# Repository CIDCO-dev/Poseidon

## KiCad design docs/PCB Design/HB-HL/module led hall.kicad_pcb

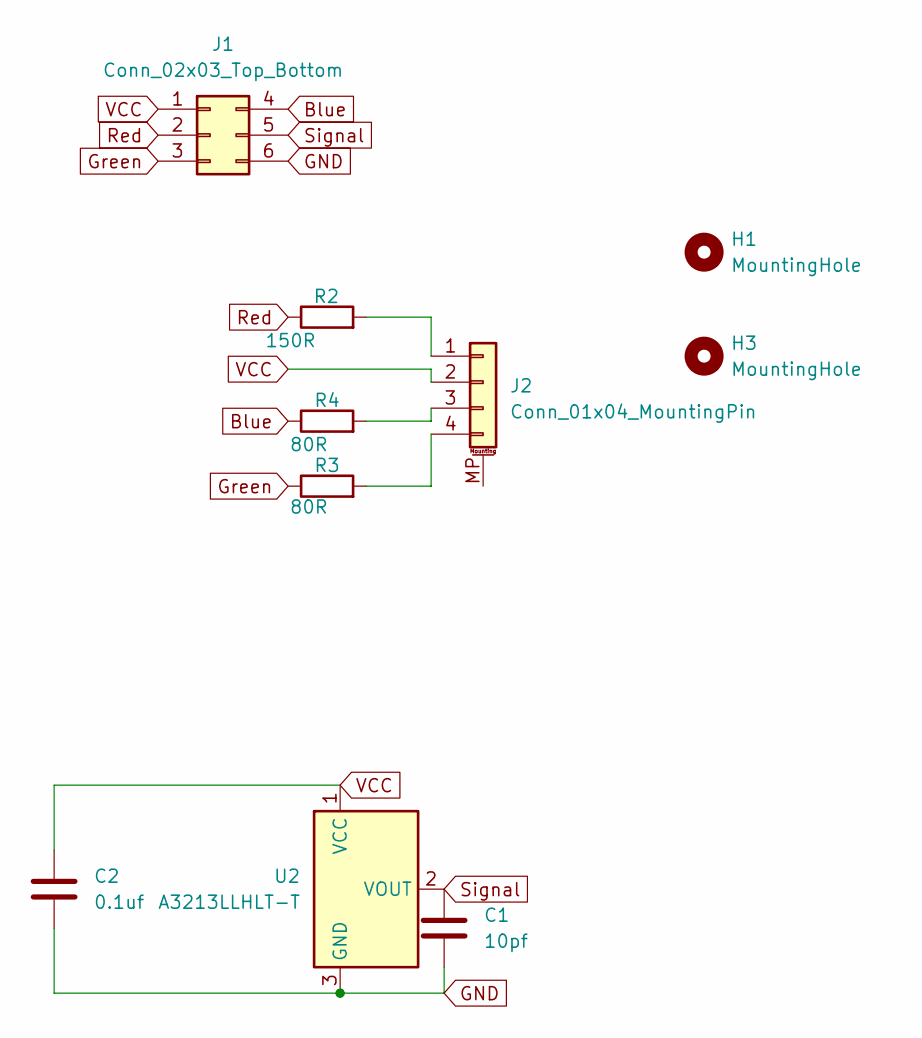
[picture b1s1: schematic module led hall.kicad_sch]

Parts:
C1: 10pf; C_1206_3216Metric
C2: 0.1uf; C_1206_3216Metric
H1, H3: MountingHole; MountingHole_4.3mm_M4
J1: Conn_02x03_Top_Bottom; IDC-Header_2x03_P2.54mm_Vertical
J2: Conn_01x04_MountingPin; TE_84952-4_1x04-1MP_P1.0mm_Horizontal
R2: 150R; R_1206_3216Metric
R3, R4: 80R; R_1206_3216Metric
U2: A3213LLHLT-T; SOT-23W

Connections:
Blue: J1.4, R4.1
GND: C1.2, C2.2, J1.6, U2.3 (GND)
Green: J1.3, R3.1
unnamed: J2.1, R2.2
unnamed: J2.3, R4.2
unnamed: J2.4, R3.2
Red: J1.2, R2.1
Signal: C1.1, J1.5, U2.2 (VOUT)
VCC: C2.1, J1.1, J2.2, U2.1 (VCC)

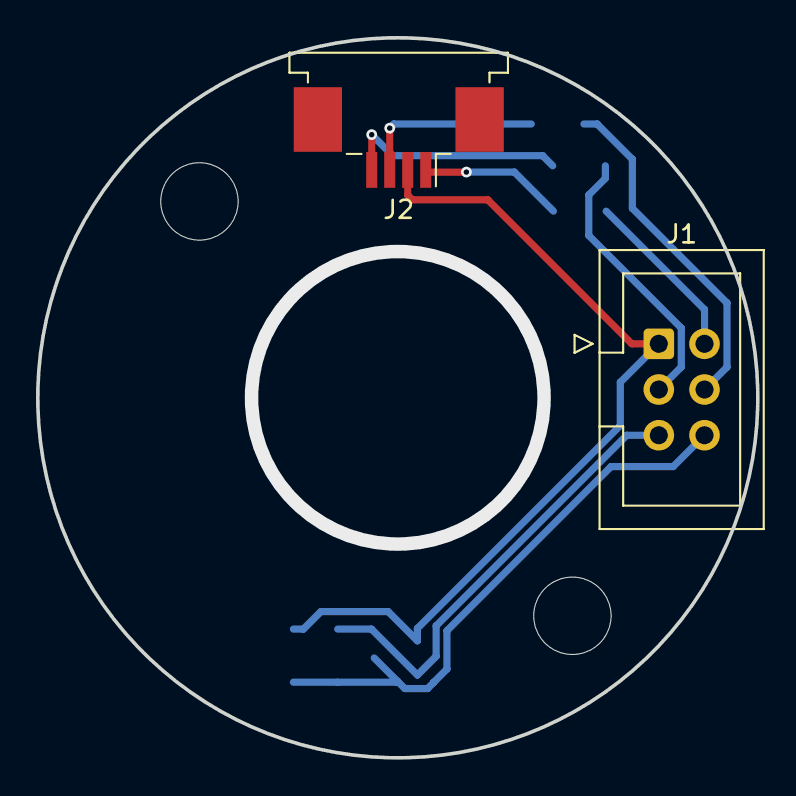
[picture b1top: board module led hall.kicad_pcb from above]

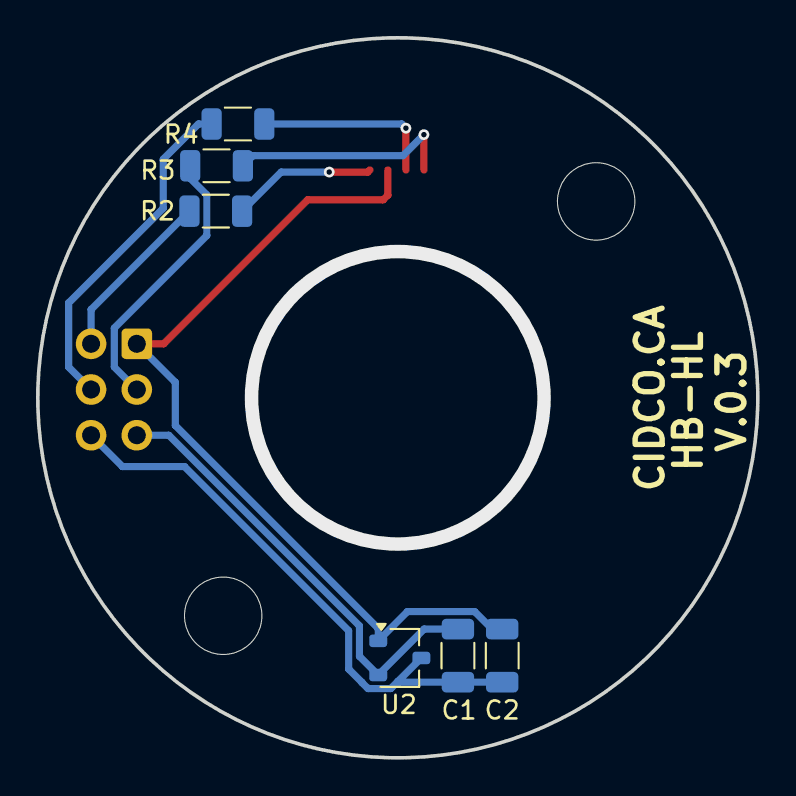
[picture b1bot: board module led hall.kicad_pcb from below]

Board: 2 copper layers, 40.0 x 40.0 mm, 10 parts (6 on the bottom side), 9 nets.

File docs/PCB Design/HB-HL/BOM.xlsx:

Comment | Designator | Footprint | JLCPCB Part #（optional）
Conn_01x04_MountingPin | J2 | TE_84952-4_1x04-1MP_P1.0mm_Horizontal | C262731
80R | R3,R4 | R_1206_3216Metric | C270896
10pf | C1 | C_1206_3216Metric | C377016
150R | R2 | R_1206_3216Metric | C2907432
A3213LLHLT-T | U2 | SOT-23W | C75884
0.1uf | C2 | C_1206_3216Metric | C841554

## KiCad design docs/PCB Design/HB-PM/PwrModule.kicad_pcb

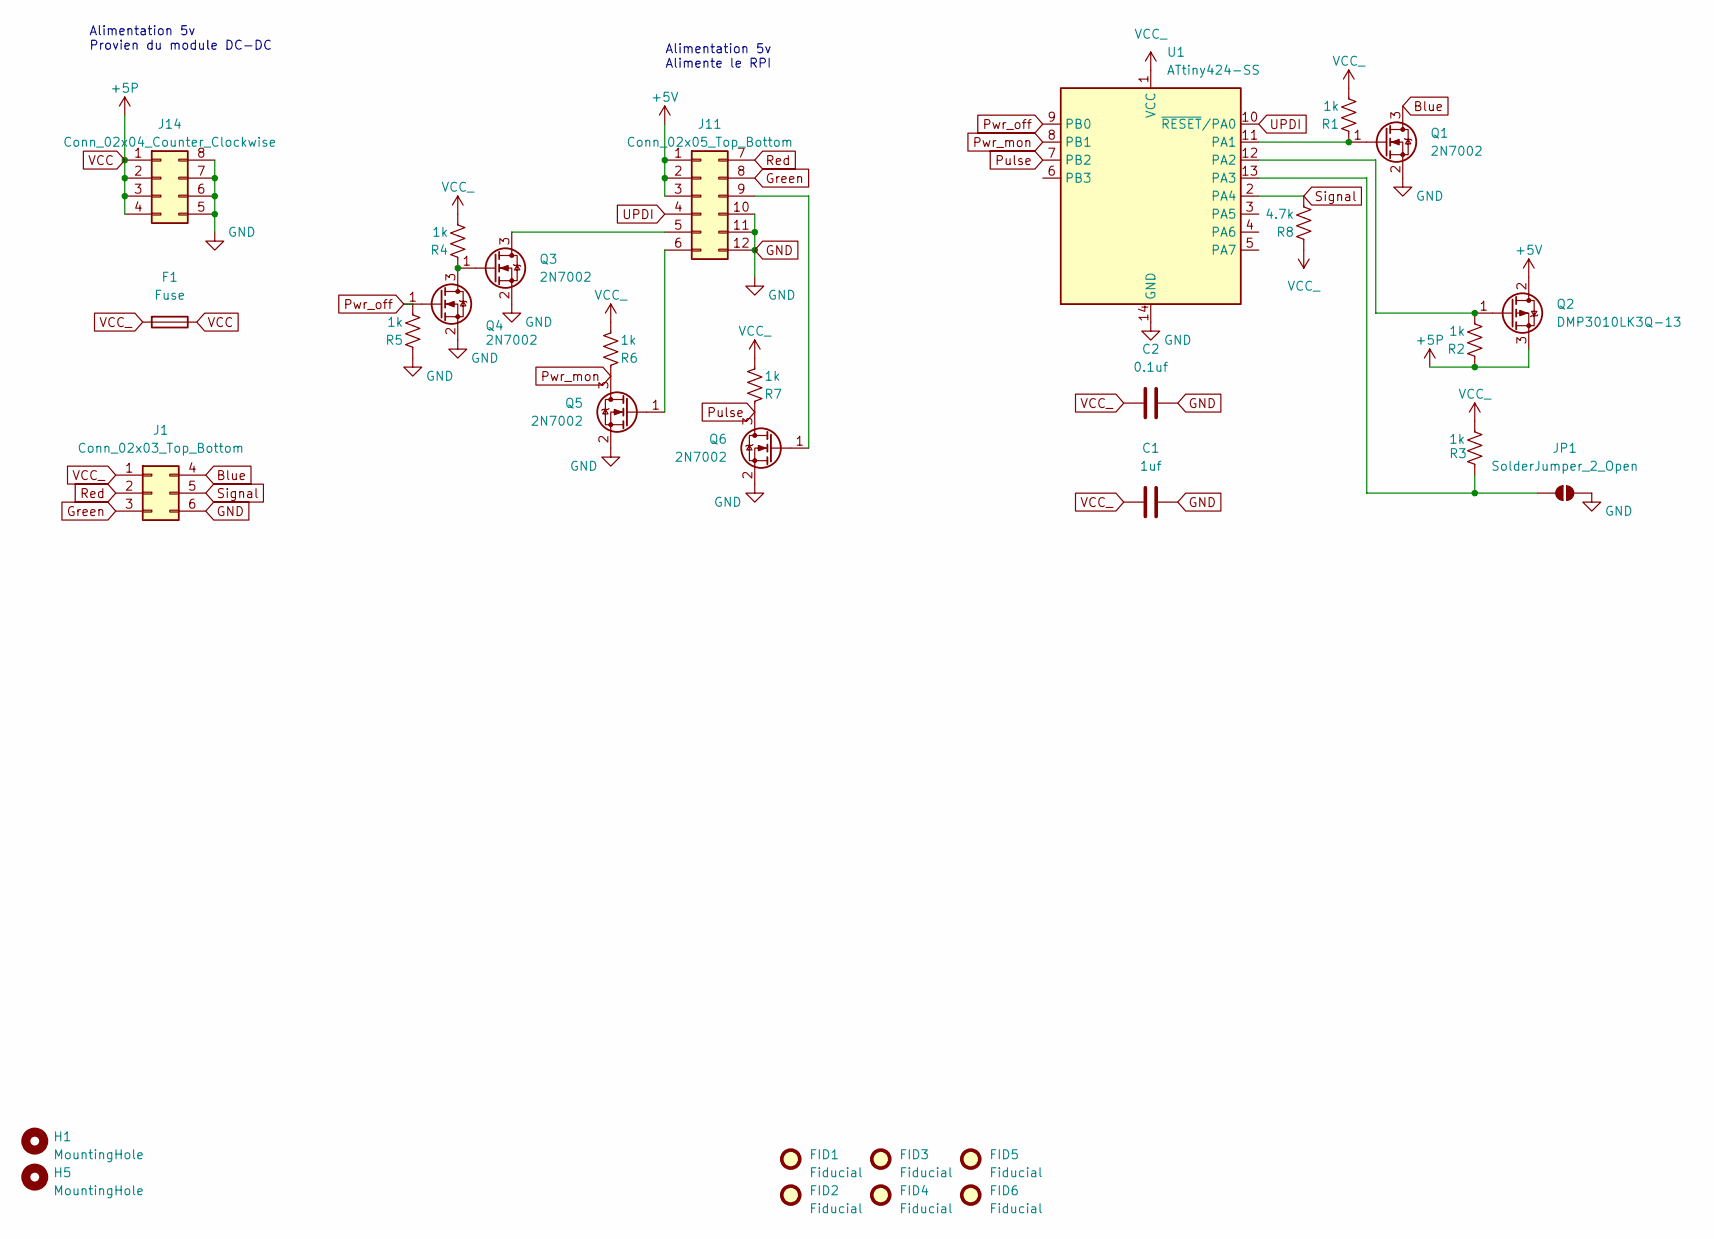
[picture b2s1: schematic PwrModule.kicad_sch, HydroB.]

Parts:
C1: 1uf; C_1206_3216Metric
C2: 0.1uf; C_1206_3216Metric
F1: Fuse; Fuse_1206_3216Metric
FID1, FID2, FID3, FID4, FID5, FID6: Fiducial; Fiducial_0.75mm_Mask2.25mm
H1, H5: MountingHole; MountingHole_2.7mm_M2.5_ISO7380_Pad
J1: Conn_02x03_Top_Bottom; IDC-Header_2x03_P2.54mm_Vertical
J11: Conn_02x05_Top_Bottom; PinHeader_2x06_P2.54mm_Vertical
J14: Conn_02x04_Counter_Clockwise; PinHeader_2x04_P2.54mm_Vertical
JP1: SolderJumper_2_Open; SolderJumper-2_P1.3mm_Open_TrianglePad1.0x1.5mm
Q1, Q3, Q4, Q5, Q6: 2N7002; SOT-23
Q2: DMP3010LK3Q-13; TO-252-2
R1, R2, R3, R4, R5, R6, R7: 1k; R_1206_3216Metric
R8: 4.7k; R_1206_3216Metric
U1: ATtiny424-SS; SOIC-14_3.9x8.7mm_P1.27mm

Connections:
+5V: J11.1, J11.2, J11.3, Q2.2 (D)
Blue: J1.4, Q1.3 (D)
GND: C1.1, C2.1, J1.6, J11.10, J11.11, J11.12, J14.5, J14.6, J14.7, J14.8, JP1.2 (B), Q1.2 (S), Q3.2 (S), Q4.2 (S), Q5.2 (S), Q6.2 (S), R5.1, U1.14 (GND)
Green: J1.3, J11.8
unnamed: J11.5, Q3.3 (D)
unnamed: J11.6, Q5.1 (G)
unnamed: J11.9, Q6.1 (G)
unnamed: JP1.1 (A), R3.1, U1.13 (PA3)
unnamed: Q1.1 (G), R1.1, U1.11 (PA1)
unnamed: Q2.1 (G), R2.2, U1.12 (PA2)
unnamed: Q3.1 (G), Q4.3 (D), R4.1
Pulse: Q6.3 (D), R7.1, U1.7 (PB2)
Pwr_mon: Q5.3 (D), R6.1, U1.8 (PB1)
Pwr_off: Q4.1 (G), R5.2, U1.9 (PB0)
Red: J1.2, J11.7
Signal: J1.5, R8.2, U1.2 (PA4)
UPDI: J11.4, U1.10 (~RESET/PA0)
VCC: F1.1, J14.1, J14.2, J14.3, J14.4, Q2.3 (S), R2.1
VCC_: C1.2, C2.2, F1.2, J1.1, R1.2, R3.2, R4.2, R6.2, R7.2, R8.1, U1.1 (VCC)

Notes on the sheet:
Alimentation 5v Alimente le RPI
Alimentation 5v Provien du module DC-DC

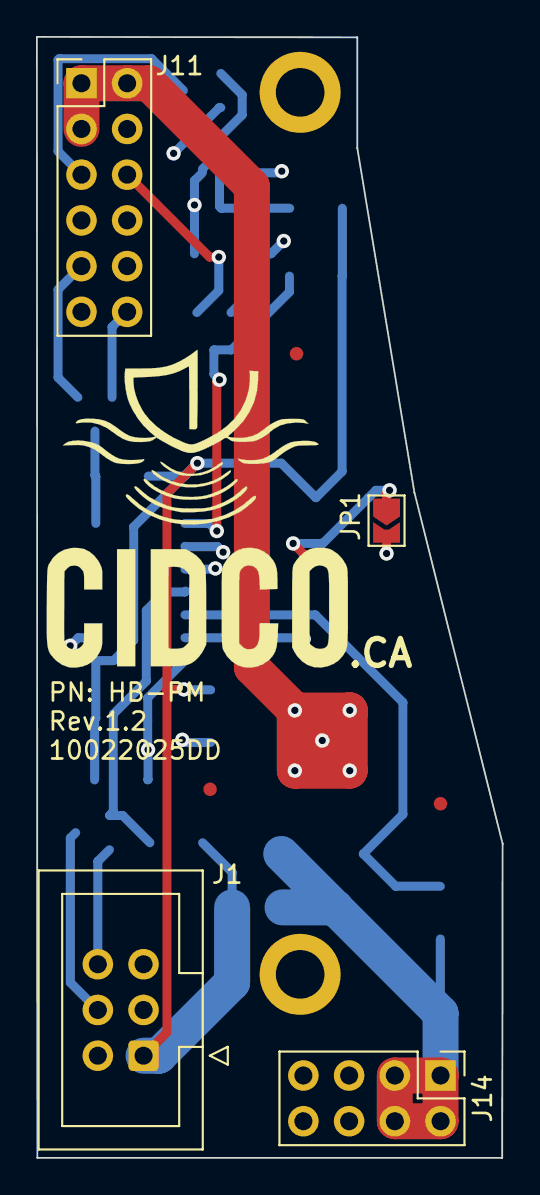
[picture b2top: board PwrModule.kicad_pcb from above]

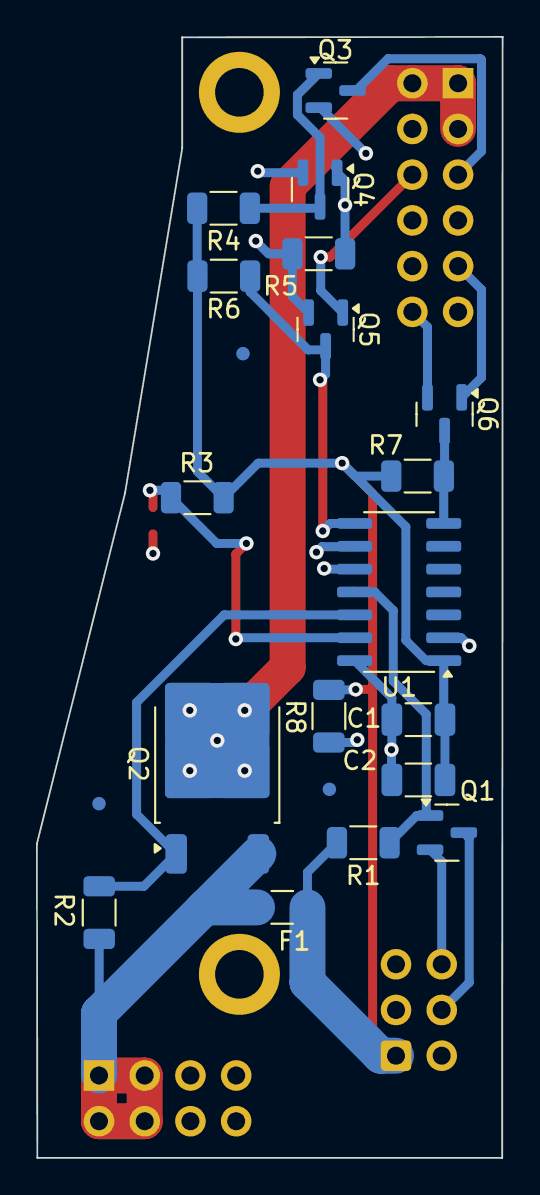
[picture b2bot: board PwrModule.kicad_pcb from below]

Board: 4 copper layers, 25.9 x 62.3 mm, 31 parts (21 on the bottom side), 19 nets.

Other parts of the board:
logo1: LOGO; logo cidco

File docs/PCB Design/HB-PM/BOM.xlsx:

Comment | Designator | Footprint | JLCPCB Part #（optional）
1uf | C1 | C_1206_3216Metric | C377070
1k | R2,R5,R3,R7,R1,R6,R4 | R_1206_3216Metric | C2889701
Fuse | F1 | Fuse_1206_3216Metric | C182308
DMP3010LK3Q-13 | Q2 | TO-252-2 | C461089
2N7002 | Q1,Q6,Q4,Q3,Q5 | SOT-23 | C22446827
0.1uf | C2 | C_1206_3216Metric | C841554
4.7k | R8 | R_1206_3216Metric | C2907499
ATtiny424-SS | U1 | SOIC-14_3.9x8.7mm_P1.27mm | C3234243

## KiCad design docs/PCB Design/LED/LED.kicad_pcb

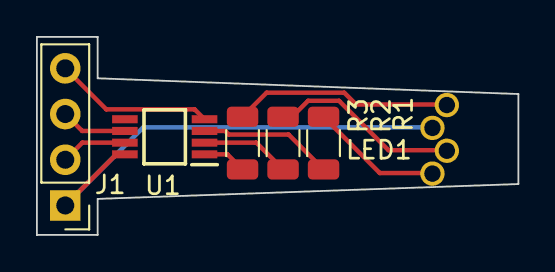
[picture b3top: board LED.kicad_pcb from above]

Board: 2 copper layers, 26.7 x 11.0 mm, 6 parts (0 on the bottom side), 10 nets.

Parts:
J1: Conn_01x04; PinHeader_1x04_P2.54mm_Vertical
LED1: HV-5RGB60; HV5RGB25
R1, R2, R3: R_US; R_1206_3216Metric
U1: PCA9533DP_02,118; SOP65P490X110-8N

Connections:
GND: J1.4, U1.4 (VSS)
unnamed: J1.1, LED1.3 (COMMON_CATHODE), U1.8 (VDD)
unnamed: J1.2, U1.7 (SDA)
unnamed: J1.3, U1.6 (SCL)
unnamed: LED1.1 (ANODE_BLUE), R1.1
unnamed: LED1.4 (ANODE_GREEN), R3.1
unnamed: LED1.2 (ANODE_RED), R2.1
unnamed: R3.2, U1.1 (LED0)
unnamed: R2.2, U1.2 (LED1)
unnamed: R1.2, U1.3 (LED2)

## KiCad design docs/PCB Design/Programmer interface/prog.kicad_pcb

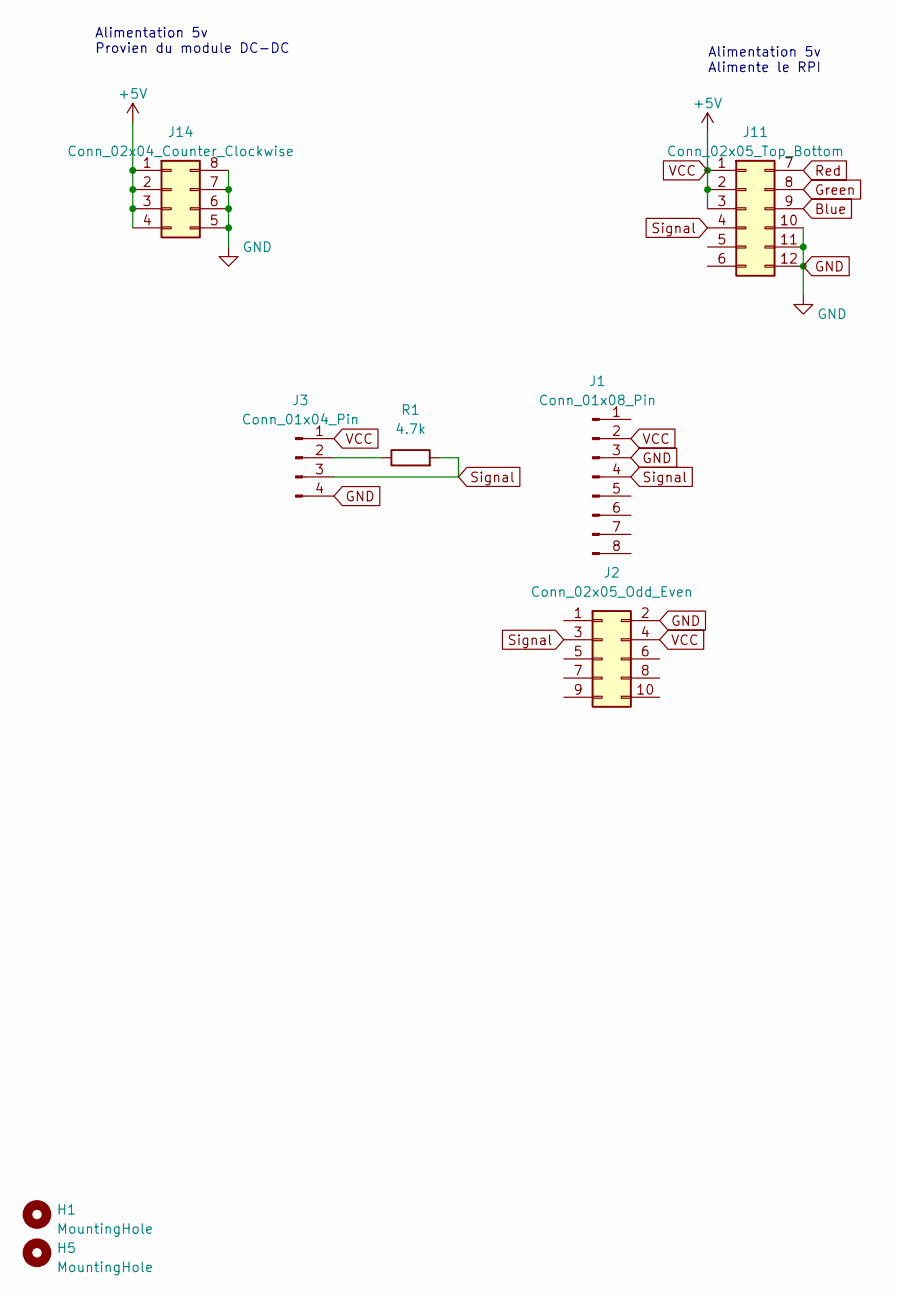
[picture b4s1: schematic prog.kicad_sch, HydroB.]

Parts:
H1, H5: MountingHole; MountingHole_2.7mm_M2.5_ISO7380_Pad
J1: Conn_01x08_Pin; PinHeader_1x08_P2.54mm_Horizontal
J2: Conn_02x05_Odd_Even; IDC-Header_2x05_P2.54mm_Vertical
J3: Conn_01x04_Pin; PinHeader_1x04_P2.54mm_Horizontal
J11: Conn_02x05_Top_Bottom; PinHeader_2x06_P2.54mm_Vertical
J14: Conn_02x04_Counter_Clockwise; PinHeader_2x04_P2.54mm_Vertical
R1: 4.7k; R_1206_3216Metric_Pad1.30x1.75mm_HandSolder

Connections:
Blue: J11.9
GND: J1.3, J2.2, J3.4, J11.10, J11.11, J11.12, J14.5, J14.6, J14.7, J14.8
Green: J11.8
unnamed: J3.2, R1.1
Red: J11.7
Signal: J1.4, J2.3, J3.3, J11.4, R1.2
VCC: J1.2, J2.4, J3.1, J11.1, J11.2, J11.3, J14.1, J14.2, J14.3, J14.4

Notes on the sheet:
Alimentation 5v Alimente le RPI
Alimentation 5v Provien du module DC-DC

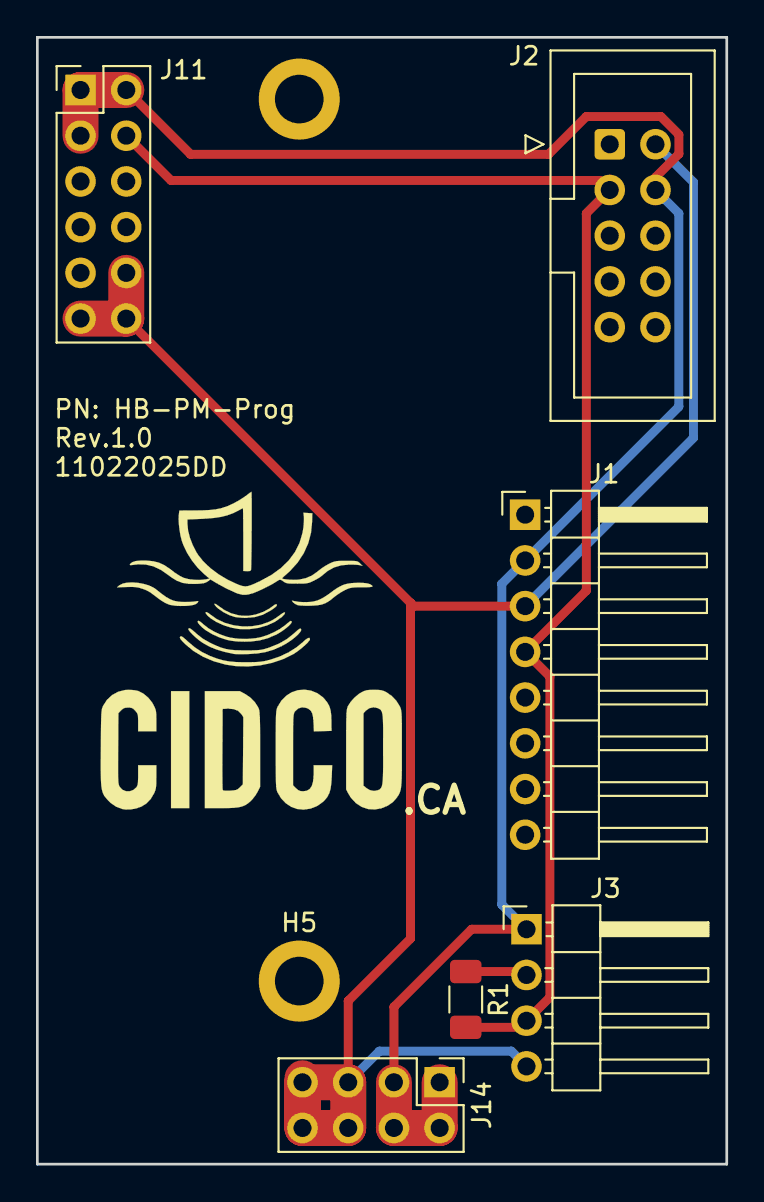
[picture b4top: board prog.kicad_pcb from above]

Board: 2 copper layers, 38.3 x 62.6 mm, 9 parts (0 on the bottom side), 4 nets.

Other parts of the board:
logo1: LOGO; logo cidco

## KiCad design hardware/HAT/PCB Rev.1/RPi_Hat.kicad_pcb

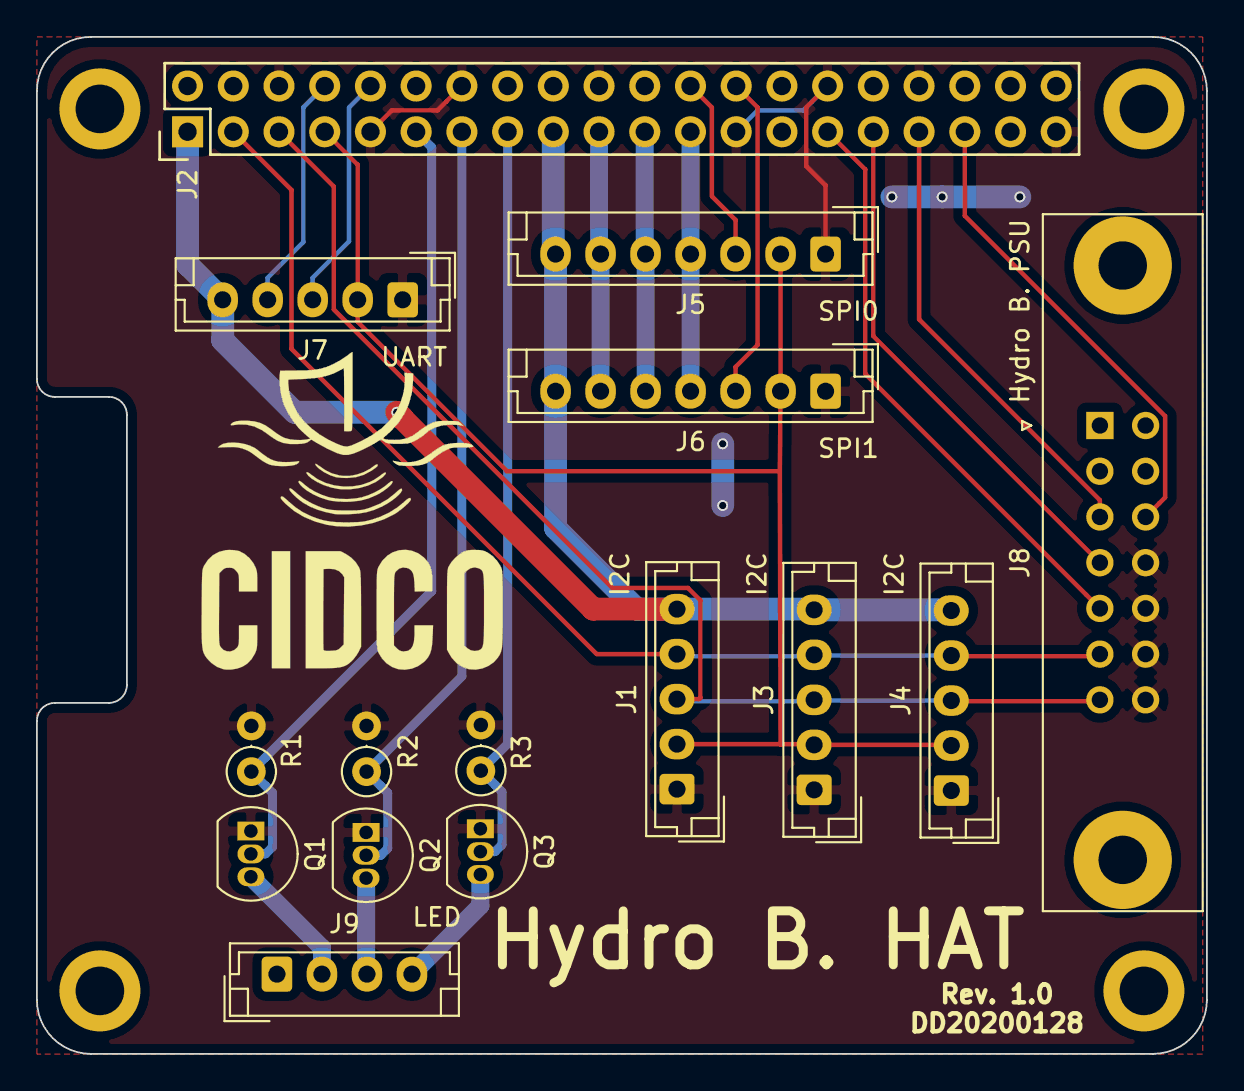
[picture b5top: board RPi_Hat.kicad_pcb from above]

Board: 2 copper layers, 65.0 x 56.5 mm, 15 parts (0 on the bottom side), 23 nets.

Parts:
J1, J3, J4, J7: Conn_01x05; JST_EH_B5B-EH-A_1x05_P2.50mm_Vertical
J2: RPi_GPIO; Pin_Header_Straight_2x20
J5, J6: Conn_01x07; JST_EH_B7B-EH-A_1x07_P2.50mm_Vertical
J8: Conn_02x07_Odd_Even; IDC-Header_2x07_P2.54mm_Vertical_Lock
J9: Conn_01x04; JST_EH_B4B-EH-A_1x04_P2.50mm_Vertical
Q1, Q2, Q3: 2N7000; TO-92_Inline
R1, R2, R3: 1k; R_Axial_DIN0207_L6.3mm_D2.5mm_P2.54mm_Vertical

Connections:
3.3V: J1.5, J2.1, J2.17, J3.5, J4.5, J5.7, J6.7, J7.5
5V: J2.2, J2.4, J8.1, J8.2, J8.3, J8.4, J9.1
12V_ON: J2.35, J8.6
24V_ON: J2.33, J8.5
C0: J2.24, J5.3
C1: J2.26, J6.3
GND: J1.1, J2.6, J2.9, J2.14, J2.20, J2.25, J2.30, J2.34, J2.39, J3.1, J4.1, J5.1, J6.1, J7.1, J8.8, J8.10, J8.12, J8.14, Q1.1, Q2.1, Q3.1, R1.2, R2.2, R3.2
LEDB: J2.15, Q3.2, R3.1
LEDG: J2.13, Q2.2, R2.1
LEDR: J2.11, Q1.2, R1.1
MISO: J2.21, J5.5, J6.5
MOSI: J2.19, J5.6, J6.6
unnamed: J9.2, Q1.3
unnamed: J9.3, Q2.3
unnamed: J9.4, Q3.3
PPS: J1.2, J2.7, J3.2, J4.2, J5.2, J6.2, J7.2
RPI_PWR_OK: J2.31, J8.7
RPI_SHDWN: J2.29, J8.9
RX: J2.10, J7.3
SCL: J1.3, J2.5, J3.3, J4.3, J8.13
SCLK: J2.23, J5.4, J6.4
SDA: J1.4, J2.3, J3.4, J4.4, J8.11
TX: J2.8, J7.4

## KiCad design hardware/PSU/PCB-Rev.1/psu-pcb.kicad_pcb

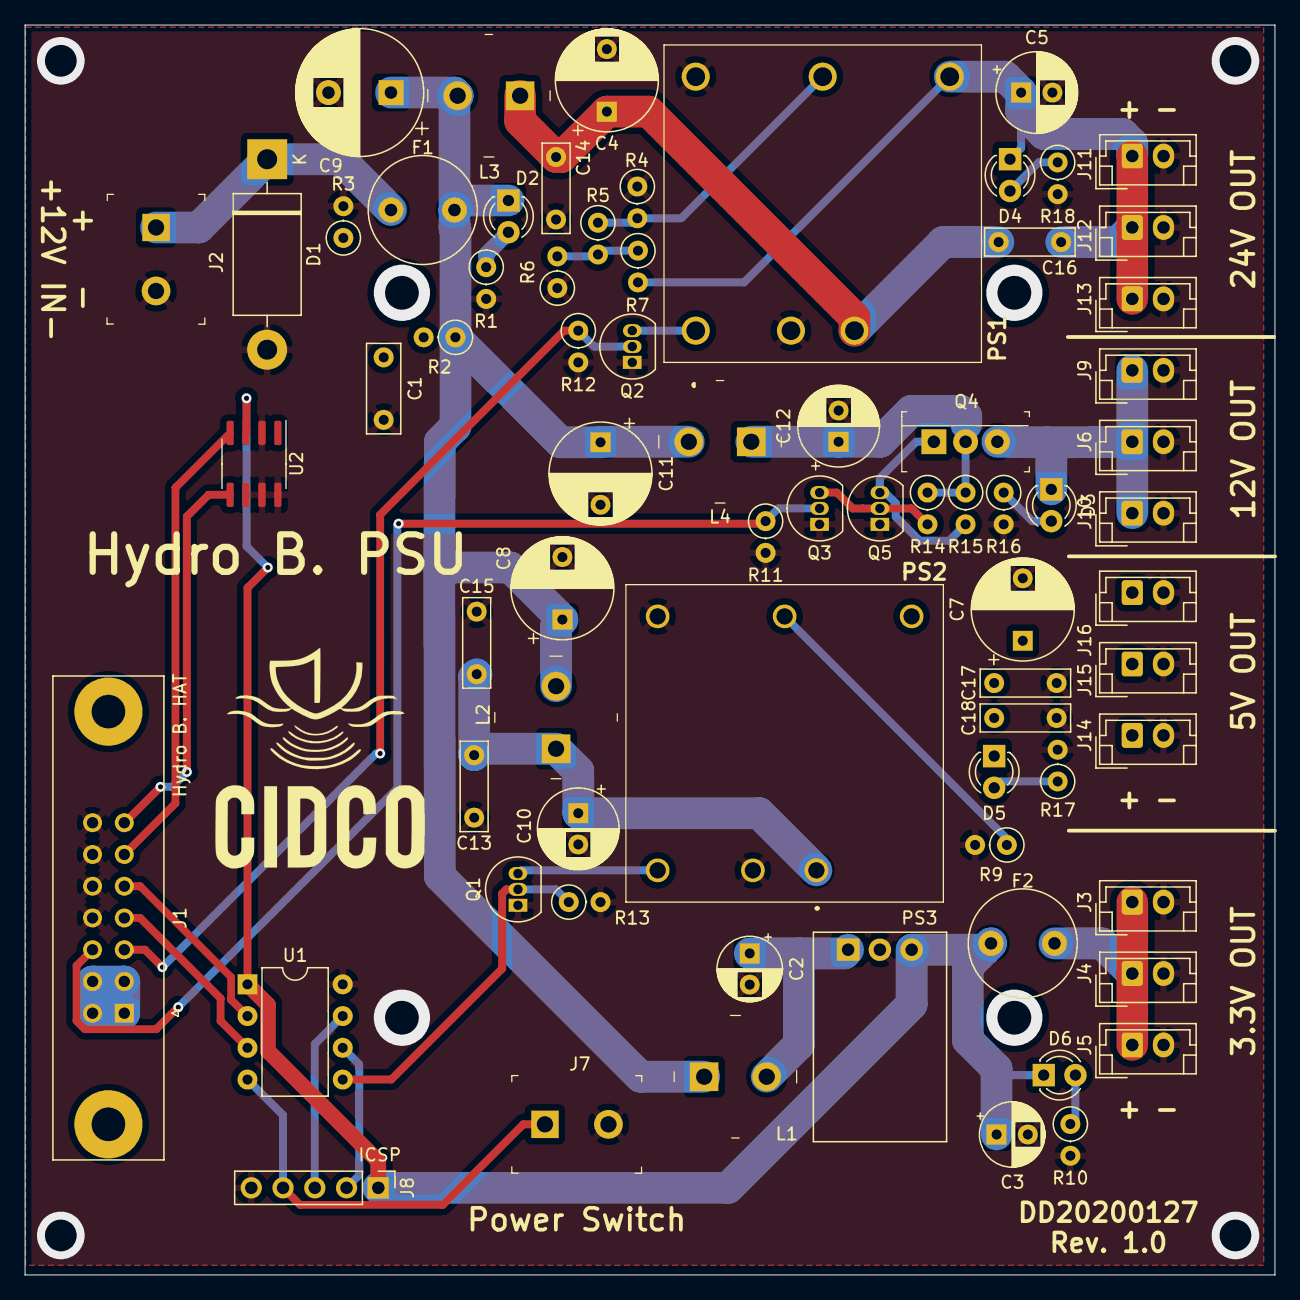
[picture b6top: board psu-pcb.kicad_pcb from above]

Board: 2 copper layers, 100.0 x 100.0 mm, 72 parts (0 on the bottom side), 34 nets.

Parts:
C1: 0.1u; C_Rect_L7.0mm_W2.5mm_P5.00mm
C2: 10u 35v; CP_Radial_D5.0mm_P2.50mm
C3: 10u 10v; CP_Radial_D5.0mm_P2.50mm
C4, C11: 100UF 50V; CP_Radial_D8.0mm_P5.00mm
C5, C12: 47UF 50V; CP_Radial_D6.3mm_P2.50mm
C7: 330uf 16v; CP_Radial_D8.0mm_P5.00mm
C8: 100UF 35V; CP_Radial_D8.0mm_P5.00mm
C9: 330UF 50V; CP_Radial_D10.0mm_P5.00mm
C10: 47UF 35V; CP_Radial_D6.3mm_P2.50mm
C13, C17: 10UF; C_Rect_L7.0mm_W2.0mm_P5.00mm
C14: 4.7UF 50V; C_Rect_L7.0mm_W2.0mm_P5.00mm
C15, C18: 0.1UF; C_Rect_L7.0mm_W2.0mm_P5.00mm
C16: 1NF 2KV; C_Rect_L7.0mm_W2.0mm_P5.00mm
D1: MBR340; D_DO-201AD_P15.24mm_Horizontal
D2, D3, D4, D5, D6: LTST-C171KRKT; LED_D3.0mm_Clear
F1, F2: 3413_0328_22; Fuse_Littelfuse_372_D8.50mm
J1: Conn_02x07_Odd_Even; IDC-Header_2x07_P2.54mm_Vertical_Lock
J2, J7: OSTTC022162; Term_Block_1x2_P5.08MM
J3, J4, J5, J6, J9, J10, J11, J12, J13, J14, J15, J16: Conn_01x02; JST_EH_B2B-EH-A_1x02_P2.50mm_Vertical
J8: Conn_01x05; PinHeader_1x05_P2.54mm_Vertical
L1: 1uh; Inductor_13R106C
L2: 13R106C; Inductor_13R106C
L3: 2.2UH 4A; Inductor_13R106C
L4: 1UH; Inductor_13R106C
PS1: PDQE20-Q24-S5-D; PDQE15Q24S5D
PS2: SKMW30F-05; SKMW30G12
PS3: OKI-78SR-3.3_1.5-W36H-C; Converter_DCDC_muRata_OKI-78SR_Horizontal
Q1, Q2, Q3, Q5: 2N7000; TO-92_Inline
Q4: FQP27P06; TO-220-3
R1, R14, R15: 10k; R_Axial_DIN0207_L6.3mm_D2.5mm_P2.54mm_Vertical
R2: 7.87k 0.1%; R_Axial_DIN0207_L6.3mm_D2.5mm_P2.54mm_Vertical
R3: 1.27k 0.1%; R_Axial_DIN0207_L6.3mm_D2.5mm_P2.54mm_Vertical
R4: XX; R_Axial_DIN0207_L6.3mm_D2.5mm_P2.54mm_Vertical
R5: 20K; R_Axial_DIN0207_L6.3mm_D2.5mm_P2.54mm_Vertical
R6: 2.87K; R_Axial_DIN0207_L6.3mm_D2.5mm_P2.54mm_Vertical
R7: 24.872K; R_Axial_DIN0207_L6.3mm_D2.5mm_P2.54mm_Vertical
R9: xx; R_Axial_DIN0207_L6.3mm_D2.5mm_P2.54mm_Vertical
R10: 220; R_Axial_DIN0207_L6.3mm_D2.5mm_P2.54mm_Vertical
R11, R12, R13: 1k; R_Axial_DIN0207_L6.3mm_D2.5mm_P2.54mm_Vertical
R16: 2k; R_Axial_DIN0207_L6.3mm_D2.5mm_P2.54mm_Vertical
R17: 560; R_Axial_DIN0207_L6.3mm_D2.5mm_P2.54mm_Vertical
R18: 3.9k; R_Axial_DIN0207_L6.3mm_D2.5mm_P2.54mm_Vertical
U1: PIC12F1501-IP; DIP-8_W7.62mm
U2: MCP3426-xSN; SOIC-8_3.9x4.9mm_P1.27mm

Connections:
3.3VOUT: F2.2, J3.1, J4.1, J5.1
5VOUT: C7.1, C17.1, C18.1, D5.1, J1.1, J1.2, J1.3, J1.4, J14.1, J15.1, J16.1, PS2.3
5v_on: Q1.2, R13.1, U1.5
12VOUT: D3.1, J6.1, J9.1, J10.1, Q4.3
12v_on: J1.6, Q3.2, R11.1
24VOUT: C5.1, C16.2, D4.1, J11.1, J12.1, J13.1, PS1.4, R7.2
24v_on: J1.5, Q2.2, R12.1
+3V3: C3.1, D6.1, F2.1, J8.1, PS3.3, U1.1, U2.3
+12V: C8.1, C9.1, C11.1, D2.1, F1.2, L1.1, L2.2, L3.2, L4.2, R2.1
GND: C1.2, C2.2, C3.2, C4.2, C5.2, C7.2, C8.2, C9.2, C10.2, C11.2, C12.2, C13.2, C14.2, C15.2, C17.2, C18.2, D1.2, J1.8, J1.10, J1.12, J1.14, J2.2, J3.2, J4.2, J5.2, J6.2, J7.2, J8.5, J9.2, J10.2, J11.2, J12.2, J13.2, J14.2, J15.2, J16.2, PS1.2, PS1.6, PS2.2, PS2.5, PS3.2, Q1.1, Q2.1, Q3.1, Q5.1, R1.2, R3.2, R4.1, R6.1, R9.2, R10.2, R11.2, R12.2, R13.2, R16.2, R17.2, R18.2, U1.8, U2.2, U2.6, U2.7, U2.8
ICSPCLK: J8.2, U1.6
ICSPDAT: J8.3, U1.7
unnamed: C2.1, L1.2, PS3.1
unnamed: C10.1, C13.1, C15.1, L2.1, PS2.1
unnamed: C12.1, L4.1, Q4.2, R14.1, R15.1
unnamed: C4.1, C14.1, C16.1, L3.1, PS1.3
unnamed: D1.1, F1.1, J2.1
unnamed: D2.2, R1.1
unnamed: D3.2, R16.1
unnamed: D4.2, R18.1
unnamed: D5.2, R17.1
unnamed: D6.2, R10.1
unnamed: PS1.1, Q2.3
unnamed: PS1.5, R4.2, R5.1
unnamed: PS2.4, R9.1
unnamed: PS2.6, Q1.3
unnamed: Q3.3, Q5.2, R14.2
unnamed: Q4.1, Q5.3, R15.2
unnamed: R5.2, R6.2, R7.1
SCK: J1.13, U2.5
SDA: J1.11, U2.4
read_sw: J7.1, J8.4, U1.4
rpi_pw_ok: J1.7, U1.3
rpi_shutdown: J1.9, U1.2

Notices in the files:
hardware/HAT/PCB Rev.1/RPi_Hat.kicad_pcb:
License: CC BY 4.0
